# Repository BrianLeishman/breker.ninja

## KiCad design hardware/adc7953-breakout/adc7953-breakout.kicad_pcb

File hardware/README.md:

# Hardware

This directory contains all of the hardware that was created for this project along with testing breakout boards

## ADC7953 Breakout Board

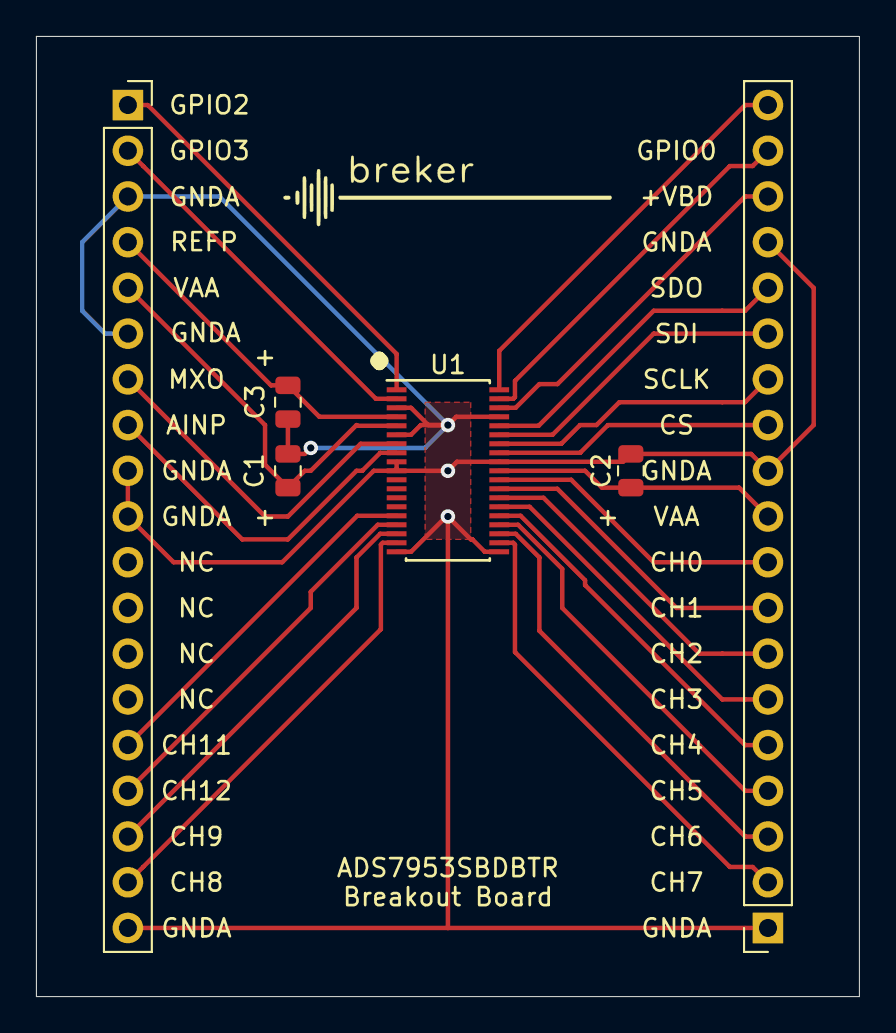
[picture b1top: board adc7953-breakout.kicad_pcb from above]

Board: 2 copper layers, 45.7 x 53.3 mm, 6 parts (0 on the bottom side), 26 nets.

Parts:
C1, C2: 1uF; C_0805_2012Metric
C3: 10uF; C_0805_2012Metric
J1, J2: Conn_01x19_Male; PinSocket_1x19_P2.54mm_Vertical
U1: ADS7953SBDBTR; TSSOP-38_4.4x9.7mm_P0.5mm

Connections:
+VBD: J2.17, U1.36
AINP: J1.8, U1.8
CH0: J2.9, U1.28
CH1: J2.8, U1.27
CH2: J2.7, U1.26
CH3: J2.6, U1.25
CH4: J2.5, U1.24
CH5: J2.4, U1.23
CH6: J2.3, U1.22
CH7: J2.2, U1.21
CH8: J1.18, U1.18
CH9: J1.17, U1.17
CH10: J1.16, U1.16
CH11: J1.15, U1.15
CS: J2.12, U1.31
GNDA: C1.2, C2.2, C3.2, J1.3, J1.6, J1.9, J1.10, J1.19, J2.1, J2.11, J2.16, U1.3, U1.6, U1.9, U1.10, U1.19, U1.20, U1.30, U1.35
GPIO0: J2.18, U1.37
GPIO1: J2.19, U1.38
GPIO2: J1.1, U1.1
GPIO3: J1.2, U1.2
MXO: J1.7, U1.7
REFP: C3.1, J1.4, U1.4
SCLK: J2.13, U1.32
SDI: J2.14, U1.33
SDO: J2.15, U1.34
VAA: C1.1, C2.1, J1.5, J2.10, U1.5, U1.29

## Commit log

2021-03-01 hudo
2021-03-01 updated config
2021-03-02 Added hardware directory and adc7953
2021-03-06 moved hardware to assets and cleaned up design
2021-03-13 the big d
2021-03-13 workflows and package.json
2021-03-14 lambda validation
2021-03-15 binary sample reading
2021-03-15 fixed workflow for api
2022-03-13 record voltage from ads
2022-03-13 faster i2c reading
2022-03-14 no idea what im doing
2022-07-25 working rust esp i2c
